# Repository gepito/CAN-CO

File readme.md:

# CAN_CO - CAN corruption device

## What CAN_CO is?

CAN_CO is a programmable device, which is capable to corrupt CAN communication frames, thus enables testing systems in the presence of communication errors.

CAN_CO is a low cost device. The employed hardware provide limited operational capabilities.

Frames corrupted on mostly statistical basis, full deterministic operation can not be guaranteed.

## What CAN_CO isn't?

CAN_CO is not a full blown failure generator system.

CAN_CO is a **non**deterministic failure generator.

## Required Hardware

We are using these hardware

- [Arduino Leonardo](https://store.arduino.cc/products/arduino-leonardo-with-headers)
- [CAN FD Shield for Arduino](https://www.longan-labs.cc/1030012.html)

## License

```
MIT License

Copyright (c) 2024 @ G-Epito EC

Permission is hereby granted, free of charge, to any person obtaining a copy
of this software and associated documentation files (the "Software"), to deal
in the Software without restriction, including without limitation the rights
to use, copy, modify, merge, publish, distribute, sublicense, and/or sell
copies of the Software, and to permit persons to whom the Software is
furnished to do so, subject to the following conditions:

The above copyright notice and this permission notice shall be included in all
copies or substantial portions of the Software.

THE SOFTWARE IS PROVIDED "AS IS", WITHOUT WARRANTY OF ANY KIND, EXPRESS OR
IMPLIED, INCLUDING BUT NOT LIMITED TO THE WARRANTIES OF MERCHANTABILITY,
FITNESS FOR A PARTICULAR PURPOSE AND NONINFRINGEMENT. IN NO EVENT SHALL THE
AUTHORS OR COPYRIGHT HOLDERS BE LIABLE FOR ANY CLAIM, DAMAGES OR OTHER
LIABILITY, WHETHER IN AN ACTION OF CONTRACT, TORT OR OTHERWISE, ARISING FROM,
OUT OF OR IN CONNECTION WITH THE SOFTWARE OR THE USE OR OTHER DEALINGS IN THE
SOFTWARE.
```

## Contact us

If you have any question, please feel free to contact [Support](mailto:can-co@g-epito.hu)

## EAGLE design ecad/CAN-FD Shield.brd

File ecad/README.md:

[Manifacturer's home](https://www.longan-labs.cc/can-bus/can-fd.html)

Eagle for [CAN FD Sheid](https://www.longan-labs.cc/1030012.html)

Based on MCP2517 and MCP2542

Click on [Longan-Labs.cc](https://www.longan-labs.cc/) to get the product you need.

Contact [support@longan-labs.cc](support@longan-labs.cc) if you need help.

# Failure generator supplement

- SOF (CAN Start of Frame) generate INT-B interrupt
- IO7 control Q1 which can pull down CAN-H, which may cause frame corruption 
- providing the right timing either arbitration or data part can be corrupted

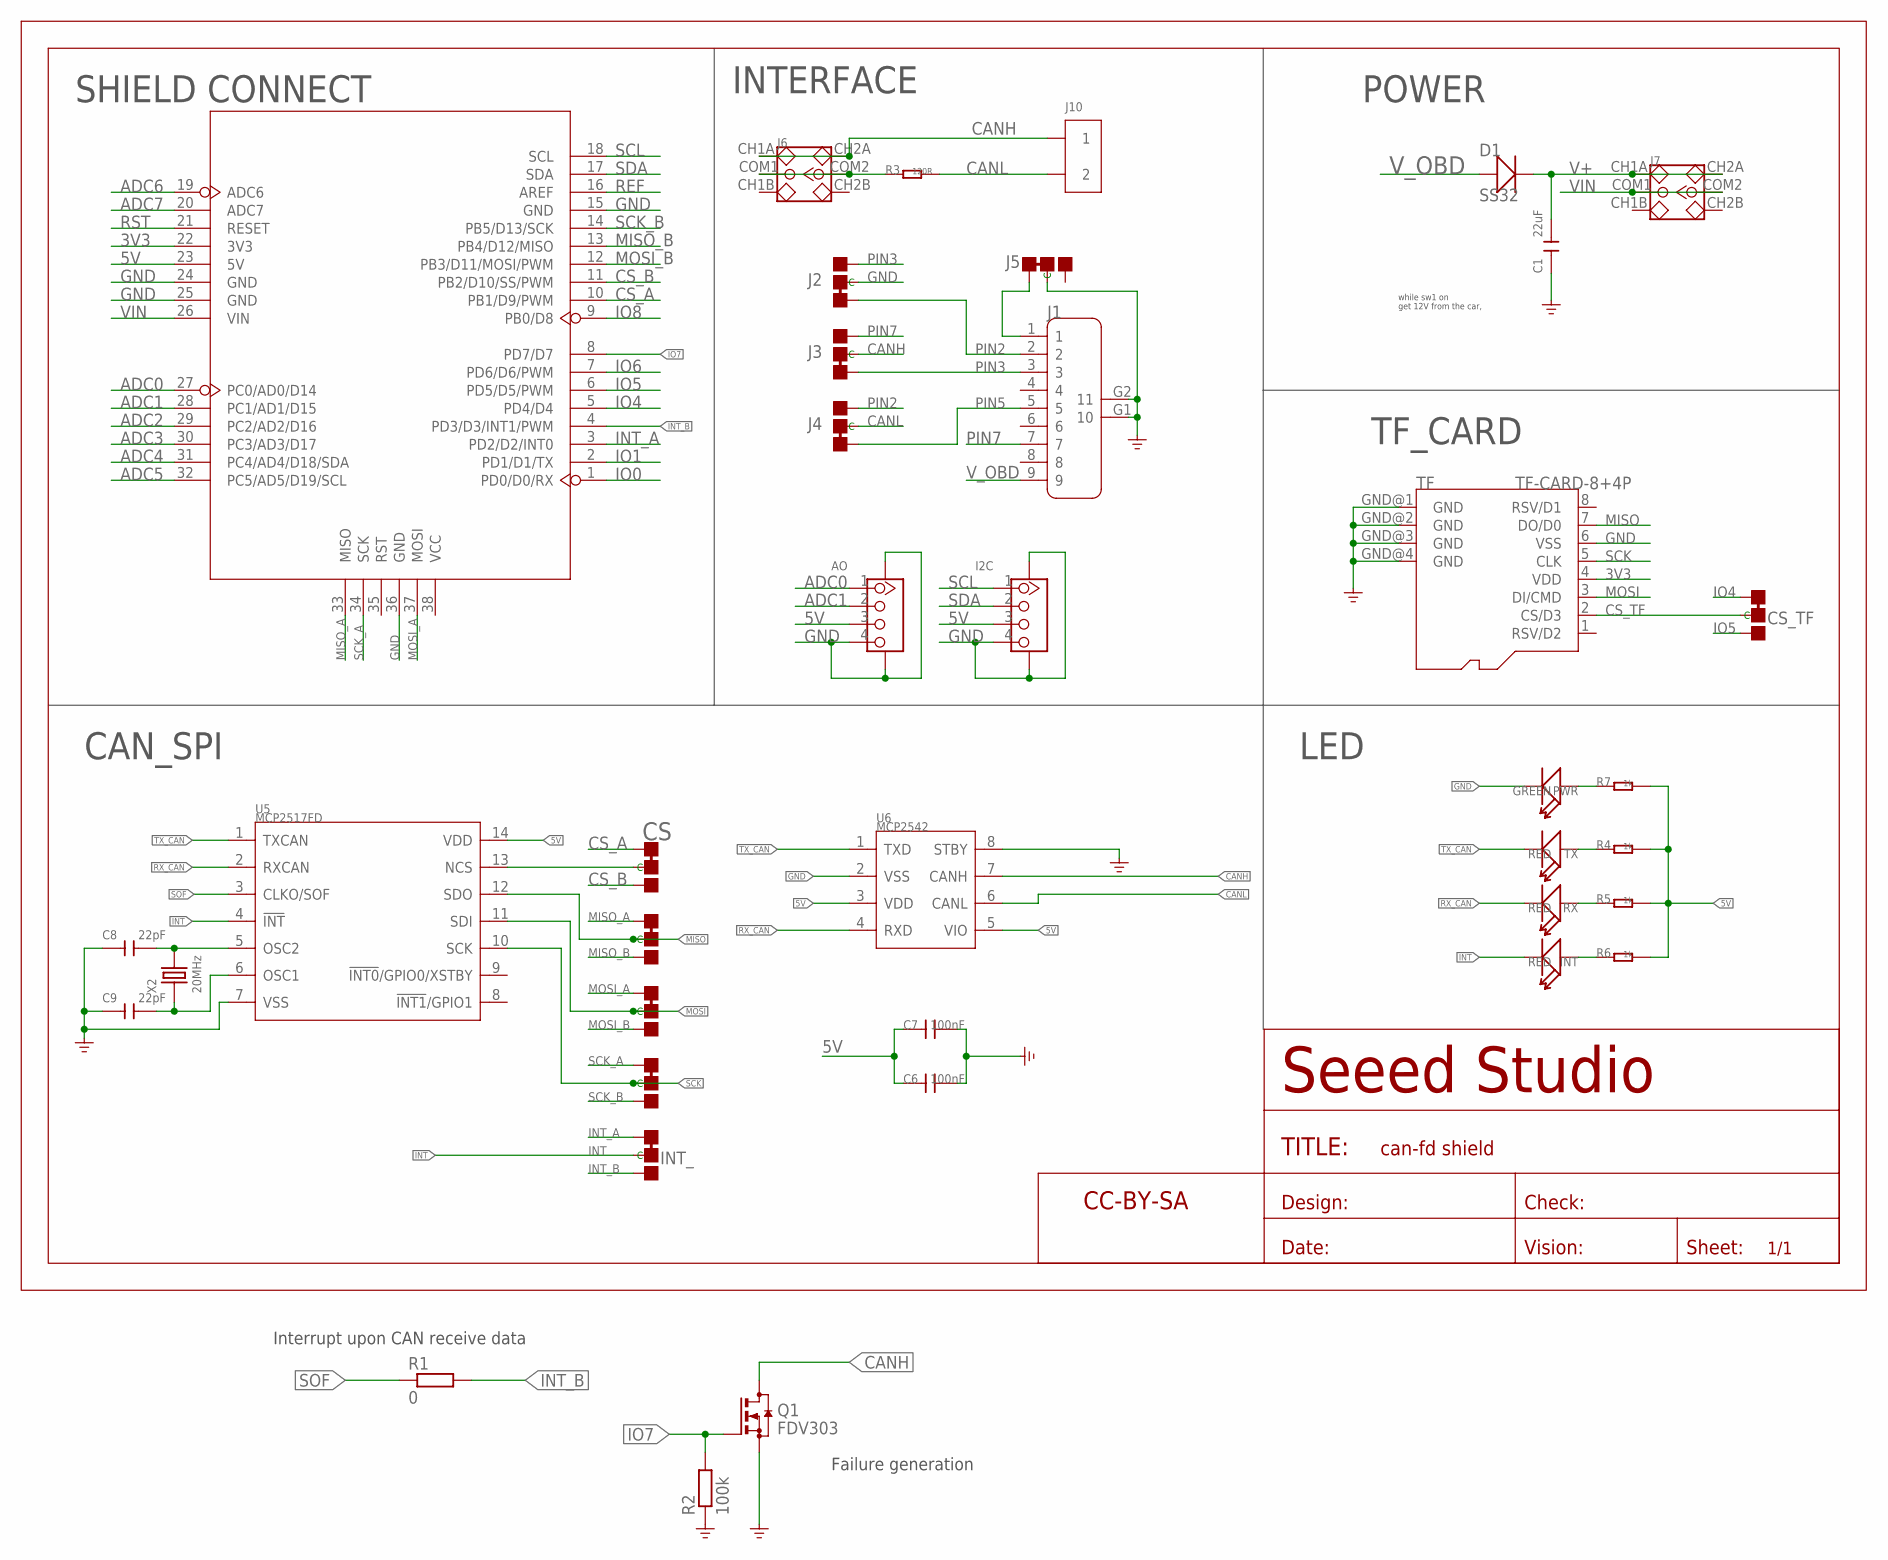
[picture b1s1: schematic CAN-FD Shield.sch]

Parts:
AO: GROVE-CONNECTOR-SMD'90D'; HW4-SMD-2.0-90D
C1: 22uF; C1206
C6, C7: 100nF; 0603
C8, C9: 22pF; C0603
CS: JUMPER-3P-SHORT; 3P-SMD-SHORT
CS_TF: JUMPER-3P-SHORT; 3P-SMD-SHORT
D1: SS32; D2010
I2C: GROVE-CONNECTOR-SMD'90D'; HW4-SMD-2.0-90D
INT: RED; LED-0603
INT_: JUMPER-3P-SHORT; 3P-SMD-SHORT
J1: DB9'MEAL'; DB9-MEAL
J2, J3, J4, J5: JUMPER-3P-SHORT; 3P-SMD-SHORT
J6, J7: SWITCH-2CH-6P; 6P-2CH-2.54-7.6X3.0
J10: SCREW-TERMINAL-2P'5.08'; H2-5.0-10.5X8.0MM
MISO: JUMPER-3P-SHORT; 3P-SMD-SHORT
MOSI: JUMPER-3P-SHORT; 3P-SMD-SHORT
PWR: GREEN; LED-0603
Q1: FDV303; SOT23
R1: 0; R0603
R2: 100k; R0603
R3: 120R; 0603
R4, R5, R6, R7: 1k; 0603
RX: RED; LED-0603
SCK: JUMPER-3P-SHORT; 3P-SMD-SHORT
TF: TF-CARD-8+4P; TF-8+4P-1.1-13.5X15MM
TX: RED; LED-0603
U4: ARDUINO-38P'WITH/-SILK'; ARDUINO-38P-WITH/-SILK-500519002
U5: MCP2517FD; SOIC14-1.27-8.6X3.9MM
U6: MCP2542; SOIC8-1.27-5X4MM
U$5: SEEEDSTUDIO-OPEN-SCH-FRAME; SEEEDSTUDIO-PCB-FRAME
X2: 20MHz; HC49US

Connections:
3V3: TF.4 (VDD), U4.22 (3V3)
5V: AO.3, C6.1, C7.1, I2C.3, R4.2, R5.2, R6.2, R7.2, U4.23 (5V), U5.14 (VDD), U6.3 (VDD), U6.5 (VIO)
ADC0: AO.1, U4.27 (PC0/AD0/D14)
ADC1: AO.2, U4.28 (PC1/AD1/D15)
ADC2: U4.29 (PC2/AD2/D16)
ADC3: U4.30 (PC3/AD3/D17)
ADC4: U4.31 (PC4/AD4/D18/SDA)
ADC5: U4.32 (PC5/AD5/D19/SCL)
ADC6: U4.19 (ADC6)
ADC7: U4.20 (ADC7)
CANH: J3.MM (C), J6.CH1A, J6.CH2A, J10.1, Q1.3 (D), U6.7 (CANH)
CANL: J4.MM (C), J10.2, R3.2, U6.6 (CANL)
CS_A: CS.11 (L), U4.10 (PB1/D9/PWM)
CS_B: CS.00 (R), U4.11 (PB2/D10/SS/PWM)
CS_TF: CS_TF.MM (C), TF.2 (CS/D3)
GND: AO.4, AO.SS1, AO.SS2, C1.1, C6.2, C7.2, C8.1, C9.1, I2C.4, I2C.SS1, I2C.SS2, J1.G1 (10), J1.G2 (11), J2.MM (C), J5.MM (C), PWR.-, Q1.2 (S), R2.1, TF.6 (VSS), TF.GND@1 (GND), TF.GND@2 (GND), TF.GND@3 (GND), TF.GND@4 (GND), U4.15 (GND), U4.24 (GND), U4.25 (GND), U4.36 (GND), U5.7 (VSS), U6.2 (VSS), U6.8 (STBY)
INT: INT.-, INT_.MM (C), U5.4 (!INT)
INT_A: INT_.11 (L), U4.3 (PD2/D2/INT0)
INT_B: INT_.00 (R), R1.2, U4.4 (PD3/D3/INT1/PWM)
IO0: U4.1 (PD0/D0/RX)
IO1: U4.2 (PD1/D1/TX)
IO4: CS_TF.11 (L), U4.5 (PD4/D4)
IO5: CS_TF.00 (R), U4.6 (PD5/D5/PWM)
IO6: U4.7 (PD6/D6/PWM)
IO7: Q1.1 (G), R2.2, U4.8 (PD7/D7)
IO8: U4.9 (PB0/D8)
MISO: MISO.MM (C), TF.7 (DO/D0), U5.12 (SDO)
MISO_A: MISO.11 (L), U4.33 (MISO)
MISO_B: MISO.00 (R), U4.13 (PB4/D12/MISO)
MOSI: MOSI.MM (C), TF.3 (DI/CMD), U5.11 (SDI)
MOSI_A: MOSI.11 (L), U4.37 (MOSI)
MOSI_B: MOSI.00 (R), U4.12 (PB3/D11/MOSI/PWM)
unnamed: PWR.+, R7.1
unnamed: R4.1, TX.+
unnamed: J6.COM1, J6.COM2, R3.1
unnamed: J1.1, J5.11 (L)
unnamed: C8.2, U5.5 (OSC2), X2.2
unnamed: CS.MM (C), U5.13 (NCS)
unnamed: R5.1, RX.+
unnamed: C9.2, U5.6 (OSC1), X2.1
unnamed: INT.+, R6.1
PIN2: J1.2, J2.11 (L), J4.00 (R)
PIN3: J1.3, J2.00 (R), J3.11 (L)
PIN5: J1.5, J4.11 (L)
PIN7: J1.7, J3.00 (R)
REF: U4.16 (AREF)
RST: U4.21 (RESET)
RX_CAN: RX.-, U5.2 (RXCAN), U6.4 (RXD)
SCK: SCK.MM (C), TF.5 (CLK), U5.10 (SCK)
SCK_A: SCK.11 (L), U4.34 (SCK)
SCK_B: SCK.00 (R), U4.14 (PB5/D13/SCK)
SCL: I2C.1, U4.18 (SCL)
SDA: I2C.2, U4.17 (SDA)
SOF: R1.1, U5.3 (CLKO/SOF)
TX_CAN: TX.-, U5.1 (TXCAN), U6.1 (TXD)
V+: C1.2, D1.-, J7.CH1A, J7.CH2A
VIN: J7.COM1, J7.COM2, U4.26 (VIN)
V_OBD: D1.+, J1.9

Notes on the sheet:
CAN_SPI
SHIELD CONNECT
INTERFACE
POWER
get 12V from the car,
while sw1 on
TF_CARD
LED
Failure generation
Interrupt upon CAN receive data

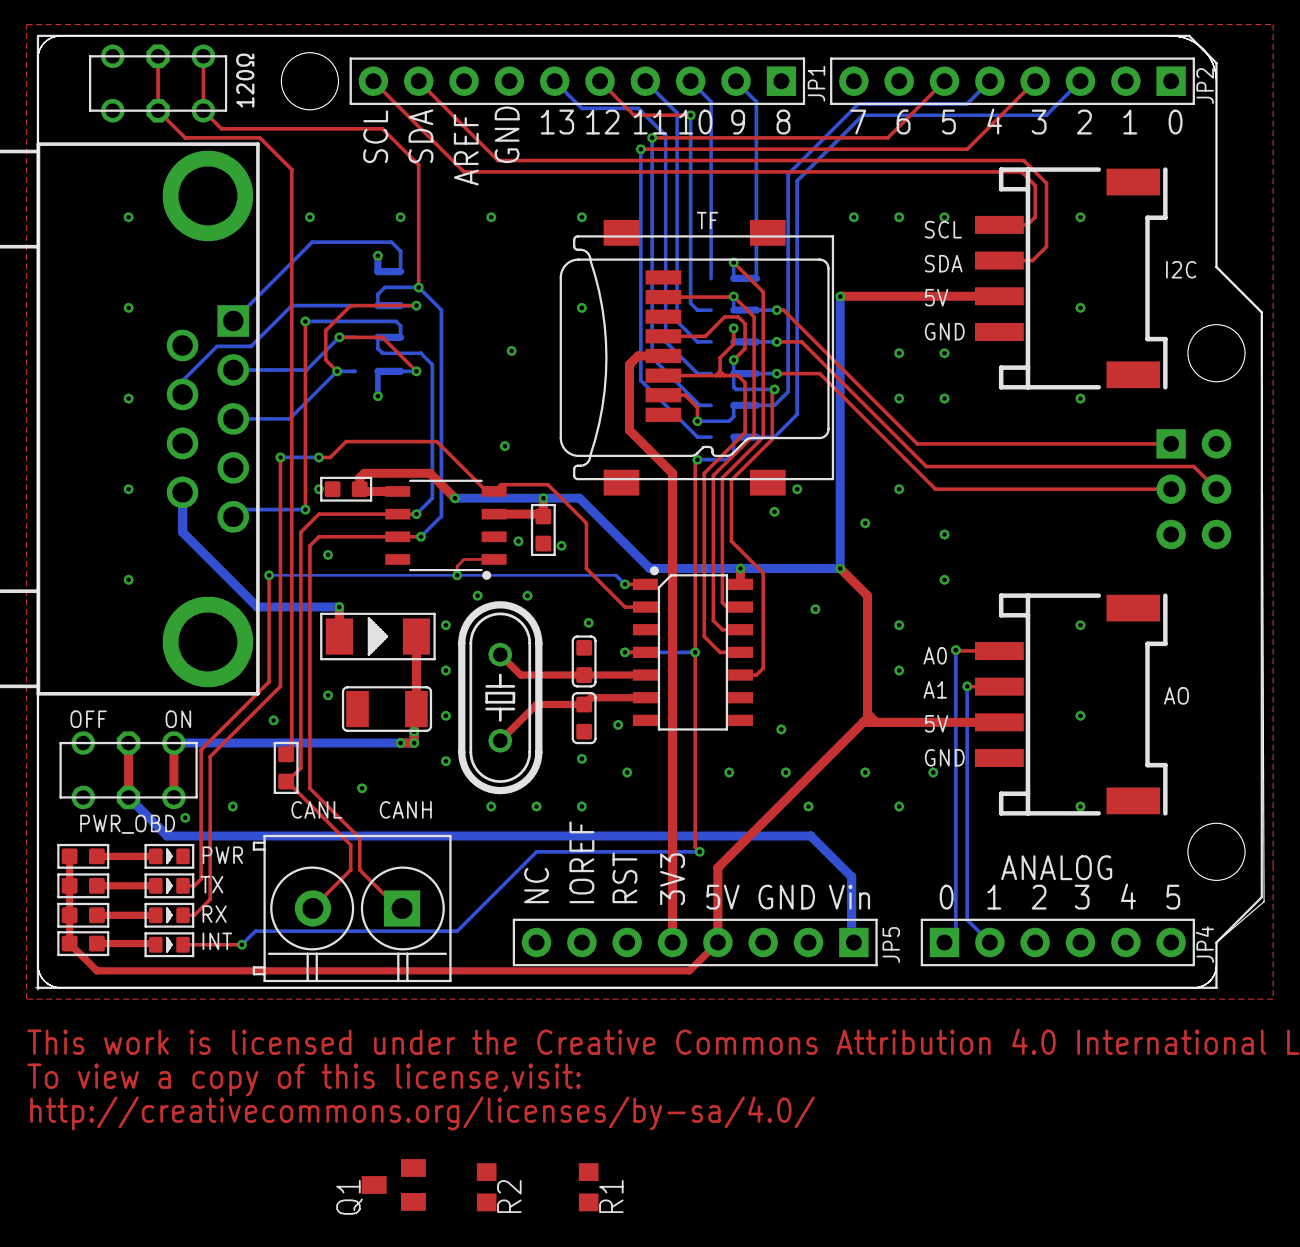
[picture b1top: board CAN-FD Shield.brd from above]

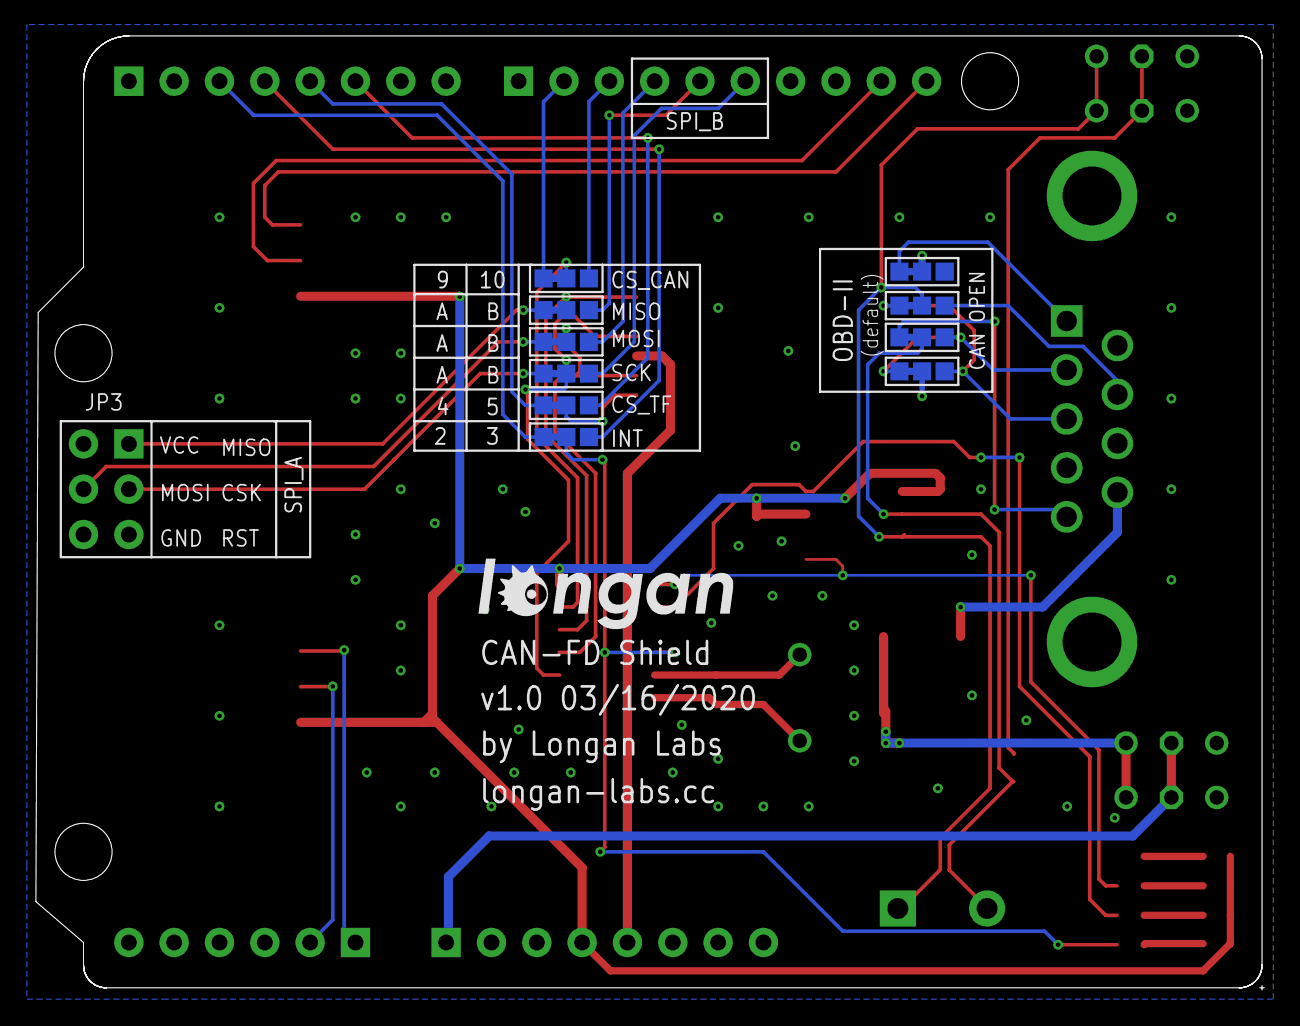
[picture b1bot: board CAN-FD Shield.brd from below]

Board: 2 copper layers, 68.8 x 53.5 mm, 41 parts (11 on the bottom side), 46 nets.

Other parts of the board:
U$1: LONGAN-SILK-SMALLER

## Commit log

2024-03-30 CANFD_SEND is adapted to Longan CAN_FD Shield
    - pin 3 is configured as SOF
    - limited retransmissin (3*)
2024-03-30 ECAD files added
2024-03-30 retransmission excercises
2024-03-30 Longan library added at the right place
2024-03-30 library restructuring completed - old files deleted
2024-04-11 interrupt_action.ino sketch added for interrupt building block
    TxAttempts field documeted in the CAN driver
2024-04-11 failure generator added to hardware design
2024-04-12 heliOS library added
2024-04-12 extending Failgen UI
2024-04-12 TimerOne library -simple interrupt timer- added
2024-04-12 heliOS_task_test created
2024-04-12 timer based "task" handling
2024-04-13 User manual added
2024-04-13 Elaborating failure generation
2024-04-14 Failure generation completed
    Documentation updated
2024-04-14 measurements removed from the repo
2024-04-14 Update LICENSE

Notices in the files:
parts and their libraries:
moudle-new: This work is licensed under the Creative Commons Attribution 4.0 International License.
To view a copy of this license,visit:
http://creativecommons.org/licenses/by-sa/4.0
moudle-new: CC-BY-SA
